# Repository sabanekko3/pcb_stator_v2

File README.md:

# pcb_stator_v2
[PCBstator v1](https://github.com/sabanekko3/pcb_stator_v1)の改良版  
ビア増強・15㎜長磁石への最適化

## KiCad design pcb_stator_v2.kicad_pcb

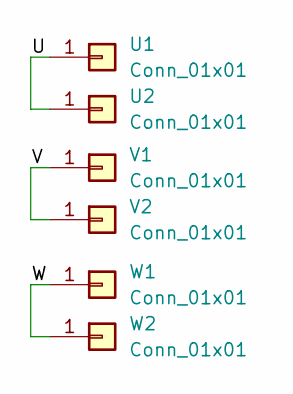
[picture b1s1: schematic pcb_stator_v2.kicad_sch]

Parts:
U1, U2: Conn_01x01; hole_pad_5x4
V1, V2: Conn_01x01; hole_pad_5x4
W1, W2: Conn_01x01; hole_pad_5x4

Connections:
/U: U1.1, U2.1
/V: V1.1, V2.1
/W: W1.1, W2.1

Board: 4 copper layers, 6 parts (0 on the bottom side), 3 nets, no tracks yet.

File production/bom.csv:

Designator,Footprint,Quantity,Value,LCSC Part #
"U1, U2, V1, V2, W1, W2",hole_pad_5x4,6,Conn_01x01,

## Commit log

2023-03-17 first
2023-03-18 add readme
2025-07-30 add stl files
